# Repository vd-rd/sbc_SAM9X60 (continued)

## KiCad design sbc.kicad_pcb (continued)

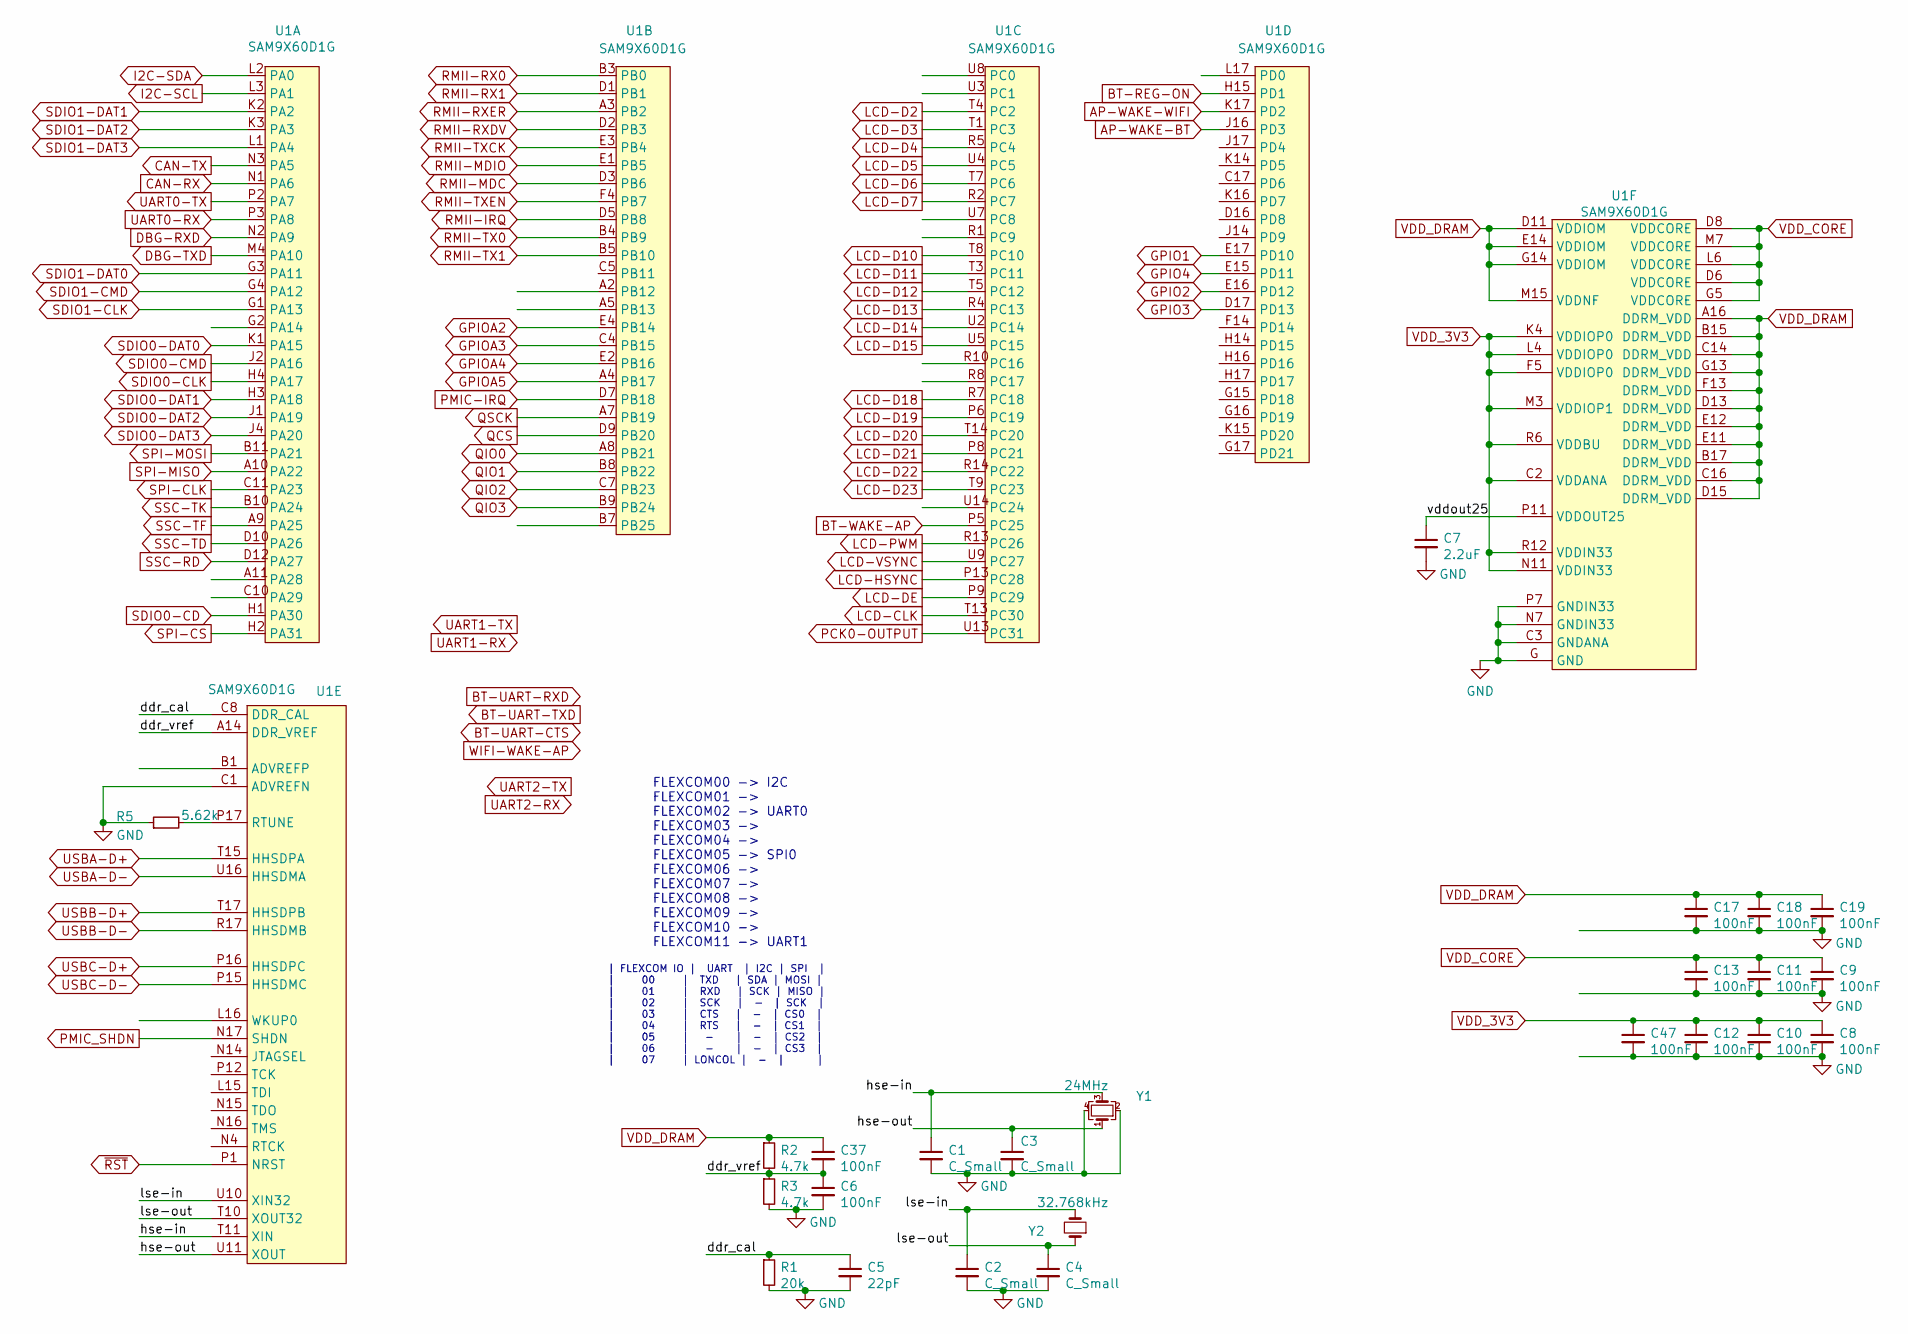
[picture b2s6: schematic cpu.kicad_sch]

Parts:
C1, C2, C3, C4: C_Small; C_0402_1005Metric
C5: 22pF; C_0402_1005Metric
C6, C8, C9, C10, C11, C12, C13, C17, C18, C19, C37, C47: 100nF; C_0402_1005Metric
C7: 2.2uF; C_0402_1005Metric
R1: 20k; R_0402_1005Metric
R2, R3: 4.7k; R_0402_1005Metric
R5: 5.62k; R_0402_1005Metric
U1: SAM9X60D1G
Y1: 24MHz; Crystal_SMD_3225-4Pin_3.2x2.5mm
Y2: 32.768kHz; Crystal_SMD_3215-2Pin_3.2x1.5mm

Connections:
/cpu/ddr_cal: C5.1, R1.1, U1.C8 (DDR_CAL)
/cpu/ddr_vref: C6.1, C37.2, R2.2, R3.1, U1.A14 (DDR_VREF)
/cpu/hse-in: C1.1, U1.T11 (XIN), Y1.3
/cpu/hse-out: C3.1, U1.U11 (XOUT), Y1.1
/cpu/lse-in: C2.1, U1.U10 (XIN32), Y2.2
/cpu/lse-out: C4.1, U1.T10 (XOUT32), Y2.1
/cpu/vddout25: C7.1, U1.P11 (VDDOUT25)
AP-WAKE-BT: U1.J16 (PD3); also elsewhere on the board
AP-WAKE-WIFI: U1.K17 (PD2); also elsewhere on the board
BT-REG-ON: U1.H15 (PD1); also elsewhere on the board
BT-WAKE-AP: U1.P5 (PC25); also elsewhere on the board
CAN-RX: U1.N1 (PA6); also elsewhere on the board
CAN-TX: U1.N3 (PA5); also elsewhere on the board
DBG-RXD: U1.N2 (PA9); also elsewhere on the board
DBG-TXD: U1.M4 (PA10); also elsewhere on the board
GND: C1.2, C2.2, C3.2, C4.2, C5.2, C6.2, C7.2, C8.2, C9.2, C10.2, C11.2, C12.2, C13.2, C17.2, C18.2, C19.2, C47.2, R1.2, R3.2, R5.1, U1.C1 (ADVREFN), U1.C3 (GNDANA), U1.G (GND), U1.N7 (GNDIN33), U1.P7 (GNDIN33), Y1.2, Y1.4; also elsewhere on the board
GPIO1: U1.E17 (PD10); also elsewhere on the board
GPIO2: U1.E16 (PD12); also elsewhere on the board
GPIO3: U1.D17 (PD13); also elsewhere on the board
GPIO4: U1.E15 (PD11); also elsewhere on the board
GPIOA2: U1.E4 (PB14); also elsewhere on the board
GPIOA3: U1.C4 (PB15); also elsewhere on the board
GPIOA4: U1.E2 (PB16); also elsewhere on the board
GPIOA5: U1.A4 (PB17); also elsewhere on the board
I2C-SCL: U1.L3 (PA1); also elsewhere on the board
I2C-SDA: U1.L2 (PA0); also elsewhere on the board
LCD-CLK: U1.T13 (PC30); also elsewhere on the board
LCD-D2: U1.T4 (PC2); also elsewhere on the board
LCD-D3: U1.T1 (PC3); also elsewhere on the board
LCD-D4: U1.R5 (PC4); also elsewhere on the board
LCD-D5: U1.U4 (PC5); also elsewhere on the board
LCD-D6: U1.T7 (PC6); also elsewhere on the board
LCD-D7: U1.R2 (PC7); also elsewhere on the board
LCD-D10: U1.T8 (PC10); also elsewhere on the board
LCD-D11: U1.T3 (PC11); also elsewhere on the board
LCD-D12: U1.T5 (PC12); also elsewhere on the board
LCD-D13: U1.R4 (PC13); also elsewhere on the board
LCD-D14: U1.U2 (PC14); also elsewhere on the board
LCD-D15: U1.U5 (PC15); also elsewhere on the board
LCD-D18: U1.R7 (PC18); also elsewhere on the board
LCD-D19: U1.P6 (PC19); also elsewhere on the board
LCD-D20: U1.T14 (PC20); also elsewhere on the board
LCD-D21: U1.P8 (PC21); also elsewhere on the board
LCD-D22: U1.R14 (PC22); also elsewhere on the board
LCD-D23: U1.T9 (PC23); also elsewhere on the board
LCD-DE: U1.P9 (PC29); also elsewhere on the board
LCD-HSYNC: U1.P13 (PC28); also elsewhere on the board
LCD-PWM: U1.R13 (PC26)
LCD-VSYNC: U1.U9 (PC27); also elsewhere on the board
unnamed: R5.2, U1.P17 (RTUNE)
PCK0-OUTPUT: U1.U13 (PC31); also elsewhere on the board
PMIC-IRQ: U1.D7 (PB18); also elsewhere on the board
PMIC_SHDN: U1.N17 (SHDN)
QCS: U1.D9 (PB20); also elsewhere on the board
QIO0: U1.A8 (PB21); also elsewhere on the board
QIO1: U1.B8 (PB22); also elsewhere on the board
QIO2: U1.C7 (PB23); also elsewhere on the board
QIO3: U1.B9 (PB24); also elsewhere on the board
QSCK: U1.A7 (PB19); also elsewhere on the board
RMII-IRQ: U1.D5 (PB8); also elsewhere on the board
RMII-MDC: U1.D3 (PB6); also elsewhere on the board
RMII-MDIO: U1.E1 (PB5); also elsewhere on the board
RMII-RX0: U1.B3 (PB0); also elsewhere on the board
RMII-RX1: U1.D1 (PB1); also elsewhere on the board
RMII-RXDV: U1.D2 (PB3); also elsewhere on the board
RMII-RXER: U1.A3 (PB2); also elsewhere on the board
RMII-TX0: U1.B4 (PB9); also elsewhere on the board
RMII-TX1: U1.B5 (PB10); also elsewhere on the board
RMII-TXCK: U1.E3 (PB4); also elsewhere on the board
RMII-TXEN: U1.F4 (PB7); also elsewhere on the board
SDIO0-CD: U1.H1 (PA30); also elsewhere on the board
SDIO0-CLK: U1.H4 (PA17); also elsewhere on the board
SDIO0-CMD: U1.J2 (PA16); also elsewhere on the board
SDIO0-DAT0: U1.K1 (PA15); also elsewhere on the board
SDIO0-DAT1: U1.H3 (PA18); also elsewhere on the board
SDIO0-DAT2: U1.J1 (PA19); also elsewhere on the board
SDIO0-DAT3: U1.J4 (PA20); also elsewhere on the board
SDIO1-CLK: U1.G1 (PA13); also elsewhere on the board
SDIO1-CMD: U1.G4 (PA12); also elsewhere on the board
SDIO1-DAT0: U1.G3 (PA11); also elsewhere on the board
SDIO1-DAT1: U1.K2 (PA2); also elsewhere on the board
SDIO1-DAT2: U1.K3 (PA3); also elsewhere on the board
SDIO1-DAT3: U1.L1 (PA4); also elsewhere on the board
SPI-CLK: U1.C11 (PA23); also elsewhere on the board
SPI-CS: U1.H2 (PA31); also elsewhere on the board
SPI-MISO: U1.A10 (PA22); also elsewhere on the board
SPI-MOSI: U1.B11 (PA21); also elsewhere on the board
SSC-RD: U1.D12 (PA27); also elsewhere on the board
SSC-TD: U1.D10 (PA26); also elsewhere on the board
SSC-TF: U1.A9 (PA25); also elsewhere on the board
SSC-TK: U1.B10 (PA24); also elsewhere on the board
UART0-RX: U1.P3 (PA8)
UART0-TX: U1.P2 (PA7)
USBA-D+: U1.T15 (HHSDPA); also elsewhere on the board
USBA-D-: U1.U16 (HHSDMA); also elsewhere on the board
USBB-D+: U1.T17 (HHSDPB)
USBB-D-: U1.R17 (HHSDMB)
USBC-D+: U1.P16 (HHSDPC)
USBC-D-: U1.P15 (HHSDMC)
VDD_3V3: C8.1, C10.1, C12.1, C47.1, U1.C2 (VDDANA), U1.F5 (VDDIOP0), U1.K4 (VDDIOP0), U1.L4 (VDDIOP0), U1.M3 (VDDIOP1), U1.N11 (VDDIN33), U1.R6 (VDDBU), U1.R12 (VDDIN33); also elsewhere on the board
VDD_CORE: C9.1, C11.1, C13.1, U1.D6 (VDDCORE), U1.D8 (VDDCORE), U1.G5 (VDDCORE), U1.L6 (VDDCORE), U1.M7 (VDDCORE); also elsewhere on the board
VDD_DRAM: C17.1, C18.1, C19.1, C37.1, R2.1, U1.A16 (DDRM_VDD), U1.B15 (DDRM_VDD), U1.B17 (DDRM_VDD), U1.C14 (DDRM_VDD), U1.C16 (DDRM_VDD), U1.D11 (VDDIOM), U1.D13 (DDRM_VDD), U1.D15 (DDRM_VDD), U1.E11 (DDRM_VDD), U1.E12 (DDRM_VDD), U1.E14 (VDDIOM), U1.F13 (DDRM_VDD), U1.G13 (DDRM_VDD), U1.G14 (VDDIOM), U1.M15 (VDDNF); also elsewhere on the board
~RST: U1.P1 (NRST); also elsewhere on the board

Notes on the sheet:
| FLEXCOM IO | UART | I2C | SPI | | 00 | TXD | SDA | MOSI | | 01 | RXD | SCK | MISO | | 02 | SCK | - | SCK | | 03 | CTS | - | CS0 | | 04 | RTS | - | CS1 | | 05 | - | - | CS2 | | 06 | - | - | CS3 | | 07 | LONCOL | - | |
FLEXCOM00 -> I2C FLEXCOM01 -> FLEXCOM02 -> UART0 FLEXCOM03 -> FLEXCOM04 -> FLEXCOM05 -> SPI0 FLEXCOM06 -> FLEXCOM07 -> FLEXCOM08 -> FLEXCOM09 -> FLEXCOM10 -> FLEXCOM11 -> UART1

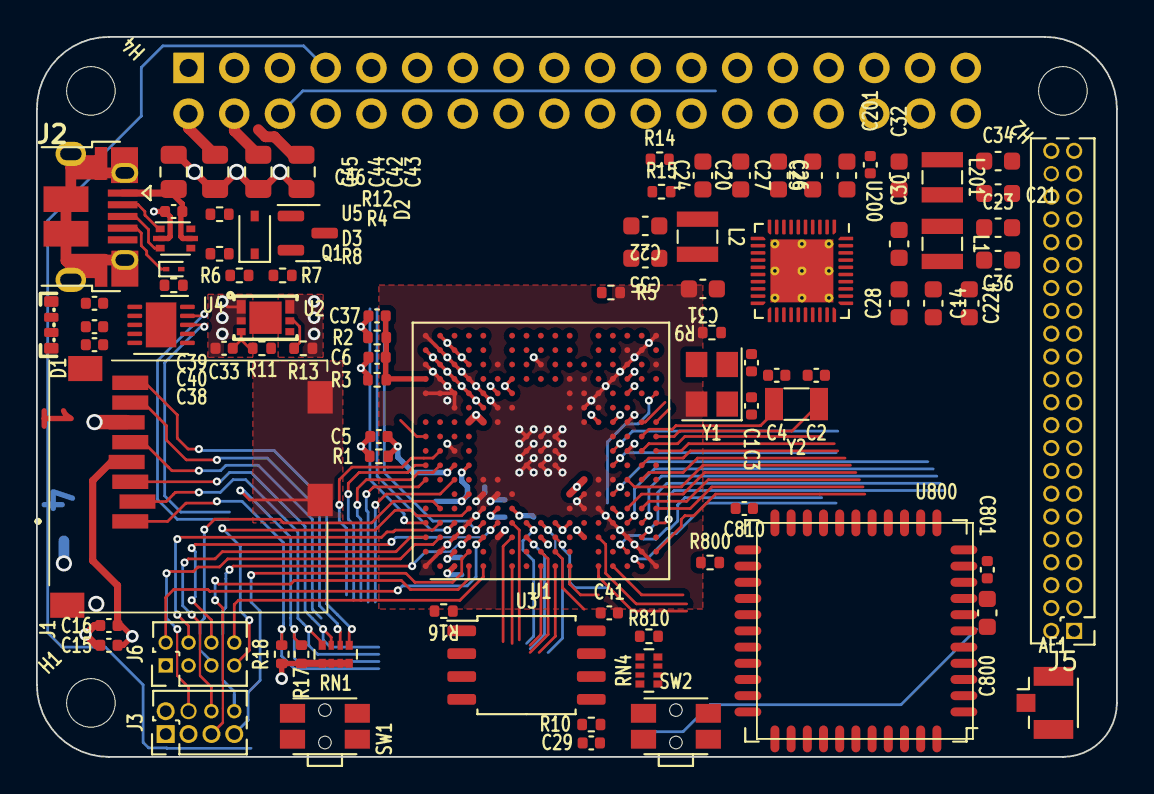
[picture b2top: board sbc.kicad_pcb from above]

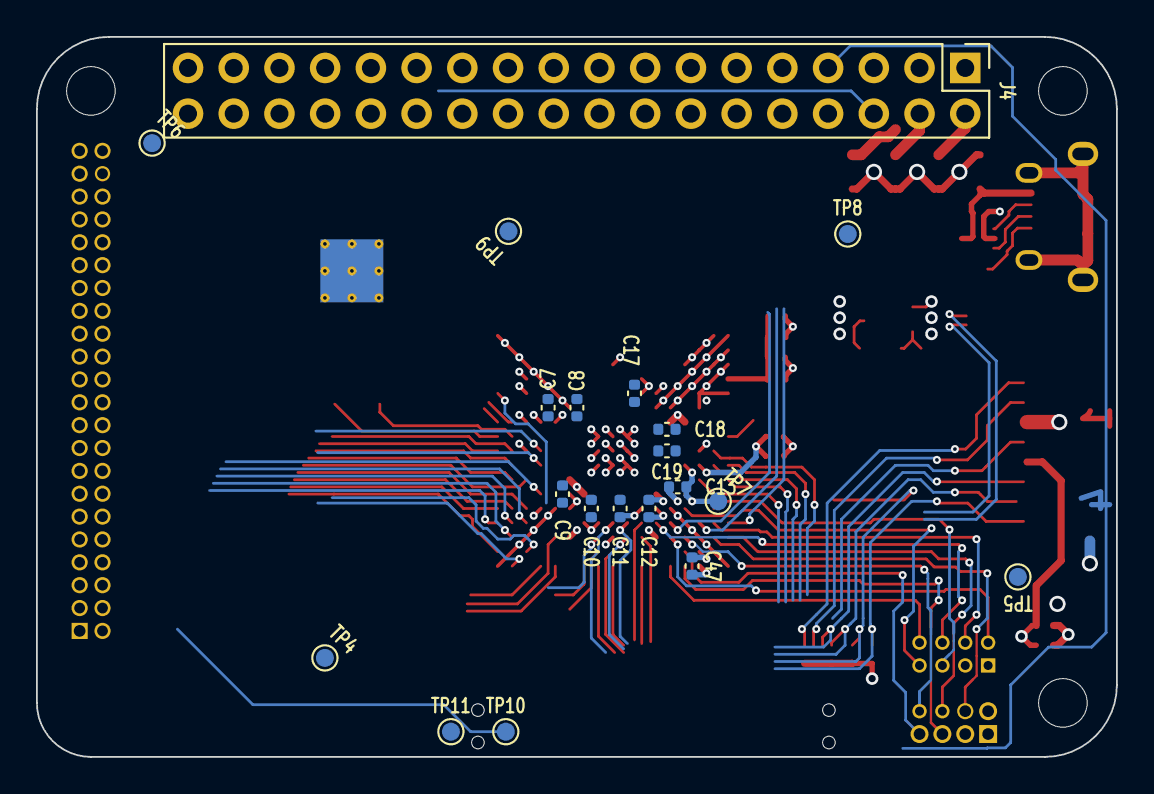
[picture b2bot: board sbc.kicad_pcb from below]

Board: 4 copper layers, 60.0 x 40.0 mm, 110 parts (20 on the bottom side), 125 nets.

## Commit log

2021-02-27 project: add sip module
2021-02-27 project: add discrete module
2021-03-02 project: add sip version footprint
2021-03-02 discrete: add decoupling caps
2021-03-02 sip: add nand
2021-03-02 sip: add pmic
2021-03-02 branch sip module
2021-03-02 add crystal for mcu
2021-03-02 prelim defining of power rails
2021-03-03 define power rails and caps
2021-03-03 pmic: define power rails
2021-03-03 add initial pin definiton
2021-03-03 add io connectors
2021-03-03 board refactoring
2021-03-03 add rmii connector
2021-03-03 add user leds
2021-03-03 add stprage options
2021-03-03 add usb lines
2021-03-04 add assembly variants
2021-05-25 add kicad filters in gitignore
2021-05-25 adding kicad project
2021-05-25 defined board shape & placement
2021-05-26 added power rails
2021-05-26 added io connectors
2021-05-26 added rmii and usb
2021-05-26 add sdcard
2021-05-26 define gpio assignments
2021-05-28 define flexcom assignment
2021-05-29 add new components
2021-06-14 added wifi sdio
2021-06-14 updated sdio connexions
2021-06-17 wifi module sch capture
2021-06-17 initial power stage routing
2021-06-24 layout improvements
2021-08-20 updated module
2021-09-02 changed board mechanical layout
2021-10-06 swapped pmic for act9845A
2021-10-06 udpdated connectors and floorplan
2021-10-10 improve component placement
2021-10-19 more routing
2021-11-13 defined connections
2021-11-14 defined more cpu signals
2021-12-12 fixed button position
2022-01-04 reposition components
2022-01-04 add nor and led driver
2022-01-04 add board render
2022-01-11 small changes in layout
2022-01-13 more routing for lcd signals
2022-01-16 add layer identification labels
2022-01-29 remove lcd fpc connector
2022-01-30 add new lcd connector
2022-02-22 define pmic zone
2024-03-19 board definition
2024-03-19 cleanup
2024-03-19 cleanup project space
2024-03-21 add and align functionality
2024-08-05 defined sip specs
